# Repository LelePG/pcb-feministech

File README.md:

# PCB-Feministech

## 🤔 O que é este projeto?

Este projeto se trata de uma placa de circuito impresso (PCB) com o logo da comunidade [Feministech](www.feministech.com.br)

A PCB foi desenvolvida utilizando o software **KiCAD** e tem o formato redondo, para acompanhar o logo da comunidade. Essa PCB também conta com leds na parte de trás da placa onde também se encontra a bateria e um botão para ligar a placa.

A placa também tem um pequeno furo na parte superior onde pode ser colocado algum tipo de argola para que ela seja utilizada como brinco ou como chaveiro.

## ⚙️ Componentes necessários para o projeto

|     Componente     | Quantidade |                                                                                       Observação                                                                                        |
| :----------------: | :--------: | :-------------------------------------------------------------------------------------------------------------------------------------------------------------------------------------: |
| Suporte de Bateria |     1      | Um exemplo do tipo de conector pode ser acessado [clicando aqui](https://br.mouser.com/ProductDetail/TE-Connectivity-Linx-Technologies/BAT-HLD-003-SMT?qs=TuK3vfAjtkVRZQIT6eTqjQ%3D%3D) |
|     LEDs 0805      |     6      |                                                                                                                                                                                         |
|       Switch       |     1      |                    Um exemplo do tipo de switch pode ser acessado [clicando aqui](https://br.mouser.com/ProductDetail/CK/PCM12SMTBR?qs=By6Nw2ByBD1OEOnWcdZb2g%3D%3D)                    |

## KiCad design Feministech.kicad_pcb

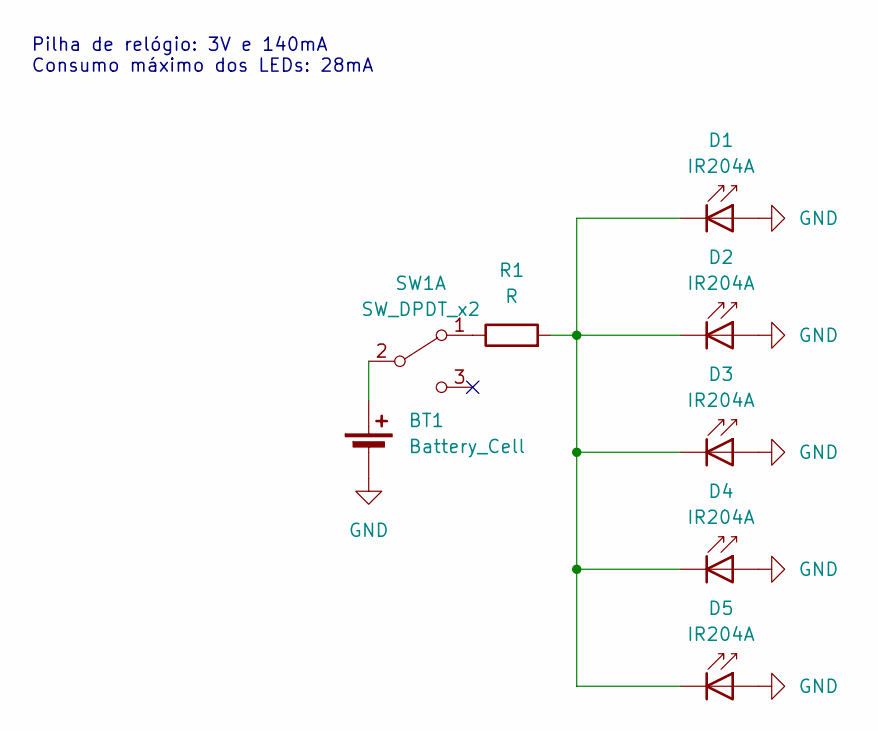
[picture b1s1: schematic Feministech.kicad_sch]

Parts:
BT1: Battery_Cell; BatteryHolder_Keystone_3002_1x2032
D1, D2, D3, D4, D5: IR204A; LED_0805_2012Metric
R1: R; R_0805_2012Metric
SW1: SW_DPDT_x2; SW_SPDT_PCM12

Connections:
GND: BT1.2 (-), D1.2 (A), D2.2 (A), D3.2 (A), D4.2 (A), D5.2 (A)
unnamed: BT1.1 (+), SW1.2 (B)
unnamed: D1.1 (K), D2.1 (K), D3.1 (K), D4.1 (K), D5.1 (K), R1.2
unnamed: R1.1, SW1.1 (A)

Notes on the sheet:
Pilha de relógio: 3V e 140mA Consumo máximo dos LEDs: 28mA

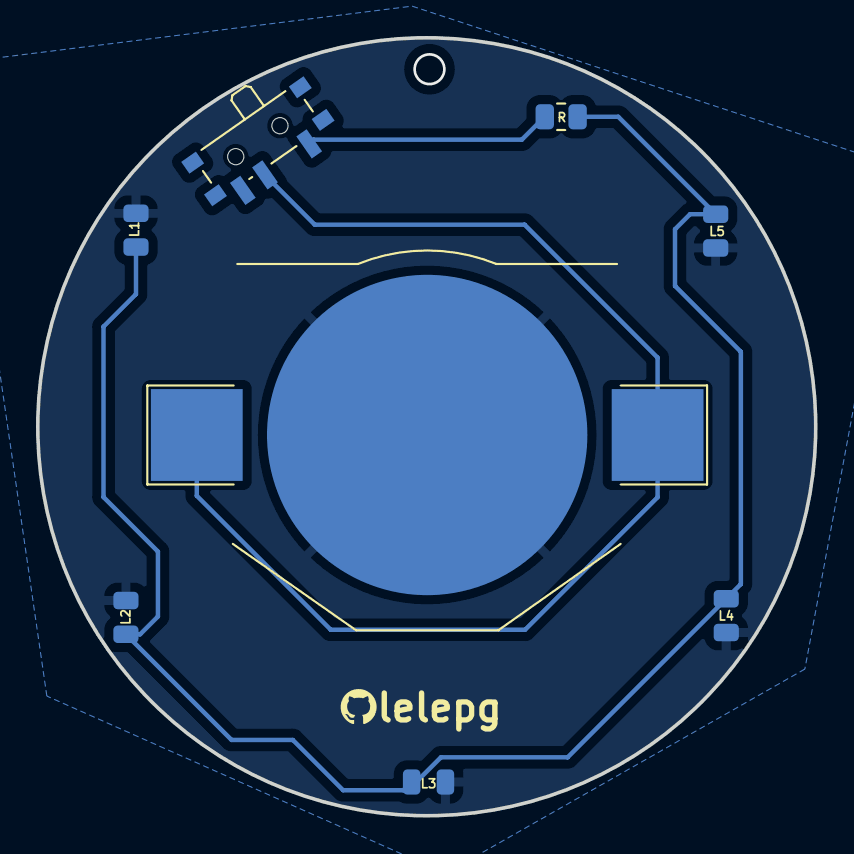
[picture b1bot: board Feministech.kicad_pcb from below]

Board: 2 copper layers, 43.2 x 43.2 mm, 9 parts (8 on the bottom side), 4 nets.

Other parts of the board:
G1: LOGO

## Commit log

2023-07-11 primeiro commit
2023-09-02 criação do README
2023-09-02 correção de formatação da tabela
